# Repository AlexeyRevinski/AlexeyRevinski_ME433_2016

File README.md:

# AlexeyRevinski_ME433_2016

This is my repository for the ME433 course at Northwestern.

04/04/2016

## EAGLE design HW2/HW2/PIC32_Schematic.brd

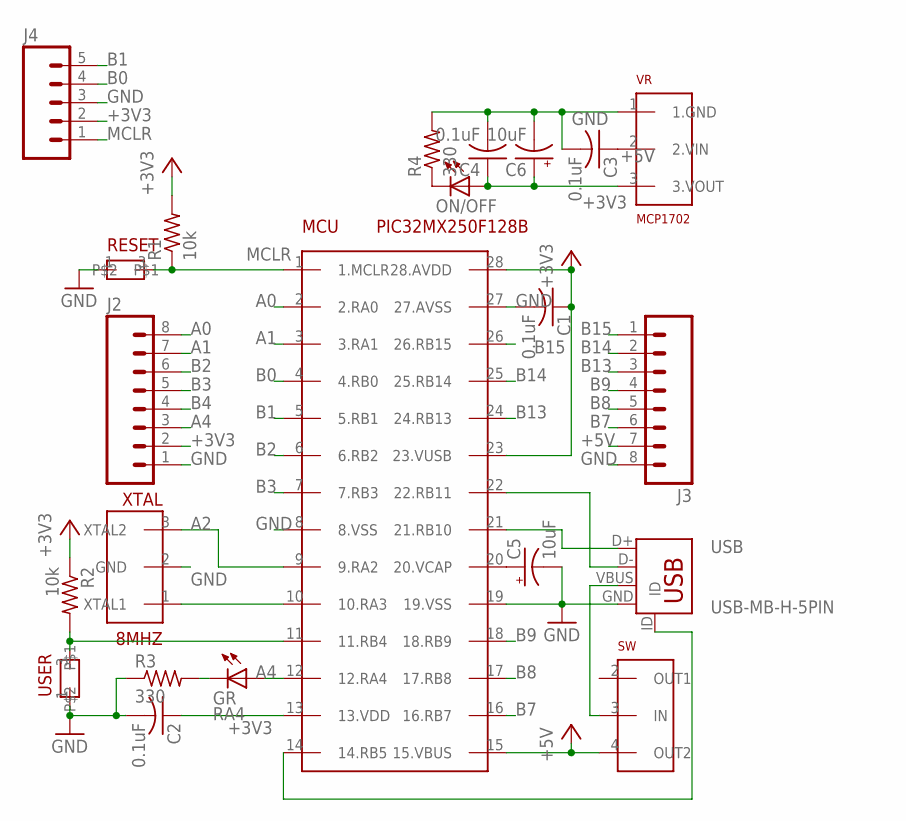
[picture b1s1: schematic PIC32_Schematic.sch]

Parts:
8MHZ: XTAL; 8MHZ_XTAL
C1, C2, C3, C4: 0.1uF; C025-024X044
C5, C6: 10uF; E2,5-6
GR: RA4; LED3MM
J2, J3: M08; 1X08_ROUND
J4: M05PTH; 1X05
MCU: PIC32MX250F128B; DIL28-3
ON/OFF: LED3MM
R1, R2: 10k; 0207/10
R3, R4: 330; 0207/10
RESET: PUSH-BUTTON
SW: SLIDE_SWITCH
USB: USB-MB-H-5PIN; USB-MB-H
USER: PUSH-BUTTON
VR: MCP1702; TO92

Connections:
+3V3: C1.1, C2.1, C4.1, C6.+, J2.2, J4.2, MCU.13 (13.VDD), MCU.23 (23.VUSB), MCU.28 (28.AVDD), ON/OFF.A, R1.2, R2.1, VR.3 (3.VOUT)
+5V: C3.1, J3.7, MCU.15 (15.VBUS), SW.4 (OUT2), VR.2 (2.VIN)
A0: J2.8, MCU.2 (2.RA0)
A1: J2.7, MCU.3 (3.RA1)
A2: 8MHZ.3 (XTAL2), MCU.9 (9.RA2)
A3: 8MHZ.1 (XTAL1), MCU.10 (10.RA3)
A4: GR.A, J2.3, MCU.12 (12.RA4)
B0: J4.4, MCU.4 (4.RB0)
B1: J4.5, MCU.5 (5.RB1)
B2: J2.6, MCU.6 (6.RB2)
B3: J2.5, MCU.7 (7.RB3)
B4: J2.4, MCU.11 (11.RB4), R2.2, USER.3
B7: J3.6, MCU.16 (16.RB7)
B8: J3.5, MCU.17 (17.RB8)
B9: J3.4, MCU.18 (18.RB9)
B13: J3.3, MCU.24 (24.RB13)
B14: J3.2, MCU.25 (25.RB14)
B15: J3.1, MCU.26 (26.RB15)
D+: MCU.21 (21.RB10), USB.D+
D-: MCU.22 (22.RB11), USB.D-
GND: 8MHZ.2 (GND), C1.2, C2.2, C3.2, C4.2, C5.-, C6.-, J2.1, J3.8, J4.3, MCU.8 (8.VSS), MCU.19 (19.VSS), MCU.27 (27.AVSS), R3.1, R4.2, RESET.1, USB.GND, USER.1, VR.1 (1.GND)
GREENLED: GR.K (C), R3.2
ID: MCU.14 (14.RB5), USB.ID
MCLR: J4.1, MCU.1 (1.MCLR), R1.1, RESET.3
unnamed: ON/OFF.K (C), R4.1
unnamed: C5.+, MCU.20 (20.VCAP)
VBUS: SW.3 (IN), USB.VBUS

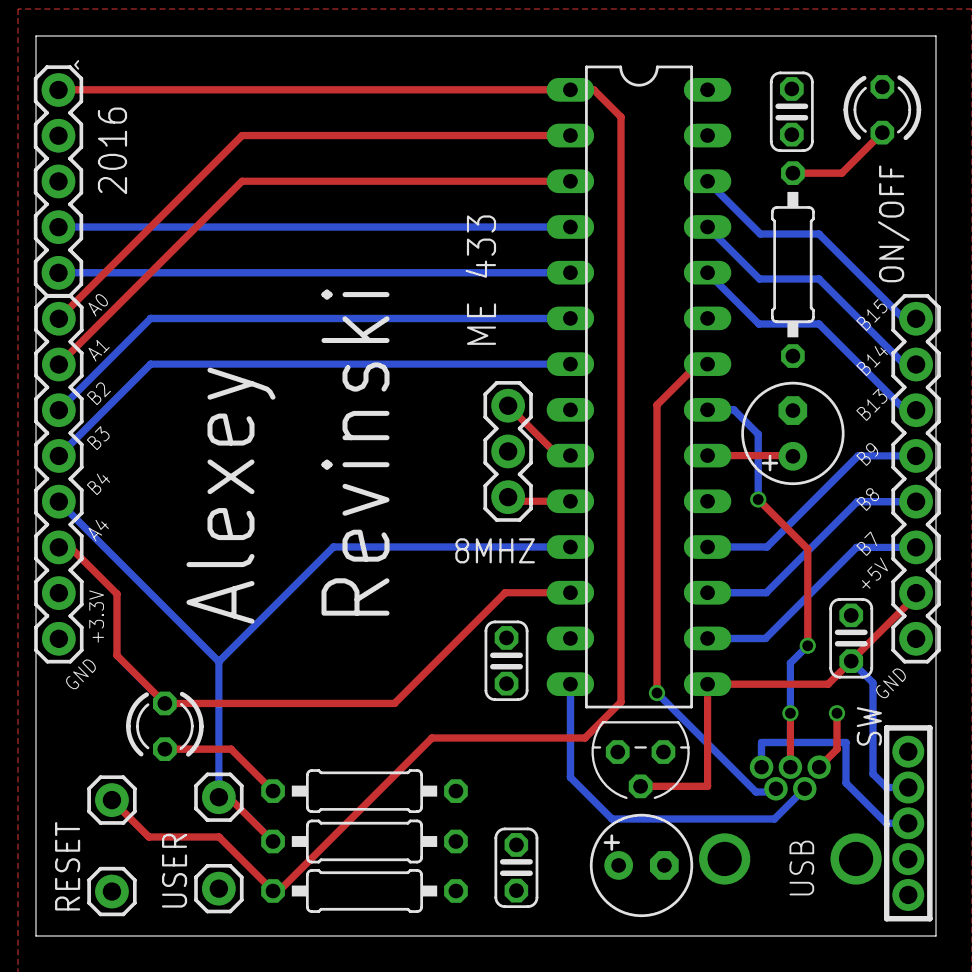
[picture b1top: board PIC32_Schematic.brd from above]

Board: 2 copper layers, 50.0 x 50.0 mm, 22 parts (0 on the bottom side), 27 nets.

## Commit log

2016-04-05 Initializing the file
2016-04-05 README edited
2016-04-05 Voltage regulator circuit built
2016-04-05 Overall circuit schematic
2016-04-05 Added files via upload
2016-04-05 Power supply oscillations (or lack thereof) of the finished circuit
2016-04-05 Default project files
2016-04-05 Finished circuit!
2016-04-05 Main.c made
2016-04-05 Template code copied and pasted
2016-04-05 Edited pragmas
2016-04-05 Main.c changed to initialize push button and LED
2016-04-05 Main changed to invert LED every 0.5 ms
2016-04-05 Main.c changed to include the push-button "stall" code
2016-04-09 HW2 Project Created
2016-04-09 Library created
2016-04-10 PIC32 Device created
2016-04-10 New schematic
    Schematic got "locked"... (?) - created new schematic, added PIC32 and
    two 8 header pins
2016-04-10 Schematic mostly connected (button switches, oscillator, and USB missing)
2016-04-11 Library is finished and new schematic was started
2016-04-11 New schematic now contains all components
2016-04-11 XTAL and some pins connected
2016-04-11 Schematic is connected further
2016-04-11 Pins 1-13 connected
2016-04-11 All PIC32 pins are now connected
2016-04-11 Schematic is complete; verification needed
2016-04-11 Entire schematic is connected (verified).
    Formatting and value setting required!
2016-04-11 Values added; schematic complete
2016-04-13 Schematic checked again; board initiated
2016-04-13 Most of the components are moved in place
2016-04-13 All components placed relative to each other
2016-04-13 Ground and +3.3V planes added (bottom and top)
2016-04-14 Most connection wired...
2016-04-14 All connections are wired
2016-04-14 Board is complete; on to error checking
2016-04-14 Error check complete.
    6 errors I can't figure out.... Drill size errors for vie holes (even
    though everything is fine) and two overlap errors that I fixed, but they
    somehow persist...
2016-04-14 Gerber files made; font somehow changed...
2016-04-14 Ready to be checked and ordered!
2016-04-20 HW4 Project folder created; main.c started
    Configuration code copied from HW1
2016-04-20 Configuration header file made
2016-04-20 I2C files started; BRG calculated
2016-04-20 Pin expander files started
2016-04-20 Most files are set up
2016-04-20 i2c reading function made
2016-04-20 i2c master write function made
2016-04-20 Expander functions started
2016-04-20 MCP23008 set up is almost finished
2016-04-20 Expander initiation function possibly complete
2016-04-20 i2c part coded; on to testing
2016-04-20 Debugging code added in various spots
2016-04-20 Neither read nor write seems to be working...
2016-04-20 BUG FOUND! ANSEL register - analog was turned off for B2 but not for B3
2016-04-21 setExpander function is complete (set/clear pins)
2016-04-21 I2C part of the homework complete!
2016-04-21 Picture of LED lighting up when button is pressed
2016-04-21 Pins for SDO, SDI, and SS are assigned
2016-04-21 spi initialization is almost done
2016-04-21 LED on/off code in main is compressed
2016-04-21 setVoltage is prepared; on to testing
2016-04-21 Testing
2016-04-22 SPI working! On to making the actual waves
2016-04-22 Triangle wave coded; on to sine wave
2016-04-22 Sine wave successfully programmed; wrong frequency
2016-04-23 Both waves have right frequency. Homework done.
2016-04-24 IMU is connected and project is set up
2016-04-24 WHO_AM_I read successfully!
2016-04-24 The control registers are almost set up
2016-04-24 CTRL registers set up!
2016-04-24 Device seems to be reading all 14 regs!
2016-04-24 Previously read 13; now reading 14 regs
2016-04-24 Renamed project folder to "HW6"
2016-04-24 char2short set up
2016-04-24 Code for 50Hz sampling rate is complete
2016-04-24 T2, OC1, and OC2 complete (but need to assign pins)
2016-04-24 TIM2, OC1, and OC2 are working
2016-04-25 XL signal obtained; refining code
2016-04-25 Code almost complete
2016-04-25 HW6 completed.
2016-04-25 Output picture obtained
2016-05-05 LCD project initialized
2016-05-05 LCD is wired and tested (color of screen changed)
2016-05-05 Tope left corner established; pixel drawn
2016-05-05 Character correctly displayed!
2016-05-05 Character displayed at desired position
2016-05-05 String successfully displayed; on to overspill checking
2016-05-05 The string is successfully printed!
2016-05-05 Hello World picture
2016-05-05 Minor update
2016-05-05 I2C2 working from previous code
2016-05-05 Gyro and Accelerometer values displayed
    The values are not fixed for the two's complement problem...
2016-05-05 Minor changes in main
2016-05-09 HW5 complete - gyro/accelerometer working properly
2016-05-09 USB Mouse complete
2016-05-11 CDC code ready for manipulating
2016-05-11 HelloWorld app initialized
2016-05-11 The first app assignment is complete
2016-05-11 Android Hello World is ready for testing
    Waiting on phone to arrive...
2016-05-13 App was successfully downloaded and tested
2016-05-23 Wheel CAD complete; on to printing
2016-05-23 HW12 (Camera App) started
2016-05-23 All code pasted
2016-05-23 Three rows implemented
2016-05-27 Wheel Printed
2016-05-27 HW11 - instead of box, final project body is completed
2016-05-27 Body design finalized; needs paint
2016-05-29 Android repo downloaded
2016-05-29 Android CDC app code is mostly fixed
2016-05-29 Minor additions
2016-06-03 CDC Homework re-done
2016-06-03 HW8 Complete
2016-06-03 Slider Bar and TextView added to CDC app
2016-06-04 Camera App edited
2016-06-05 CameraApp: Flashlight button added
2016-06-05 AndroidCDC controls motor speed with SeekBar
2016-06-05 CDC app controls wheel forwards and backwards
2016-06-05 CameraApp used as base
2016-06-05 CDC App is actually used as a base for merging
2016-06-05 Graphically merged; merging code
2016-06-05 Camera and CDC apps successfully merged!
2016-06-06 TechCup App is done!
2016-06-06 HW15 complete!
2016-06-08 HW 16 complete!
